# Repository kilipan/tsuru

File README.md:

# 鶴の恩返し (Tsuru No Ongaeshi)
A cute lil 3-row, katana-staggered keyboard with ISO-Enter compat :)

## Versions
As of now there exist two confirmed versions in this repo:
- SAMD21 version (wired, ZMK only, you will have to flash a bootloader!)
- CH552T version (wired, FAK only)

An untested wireless version can be found in the ble branch.

An STM32F072 mod of the original SAMD21 version is available [here](https://github.com/calvin-mcd/tsuru-STM).

## Layout Options
Note: The CH552T version does not support the encoder!

## Firmware
Firmware can be found in my respective repos:
- [FAK config](https://github.com/kilipan/fak-config/tree/main/keyboards/tsuru)
- [ZMK config](https://github.com/kilipan/zmk-config-tsuru)

## Cases
A beatiful wedge case (**NOT** pictured above) was made by DizzySkizzo (`dizzyskizzo1337` on Discord), who graciously allowed me to make it available under the same license. See the `case` directory.

A super fun case with a key strap and transport shell made by krisenplan is available [on printables](https://www.printables.com/de/model/946165-tsuru-travel-keyboard-case)!

Two great cases made by [Seirin-Blu](https://github.com/seirin-blu) are available here:
- [Tsuru MFR2](https://github.com/seirin-blu/Tsuru-MFR2)
- [SK-Tsuru](https://github.com/seirin-blu/SK-Tsuru)

## Availability
All files are provided under CERN-OHL-S license. Feel free to build your own!

## Thanks
Thank you Pete Johanson for letting me use the SAMD21 schematic and zmk config from the [samd21pad](https://github.com/petejohanson/samd21pad/) and for all the help getting the bootloader onto the chip!
This would've never gotten anywhere without your help <3

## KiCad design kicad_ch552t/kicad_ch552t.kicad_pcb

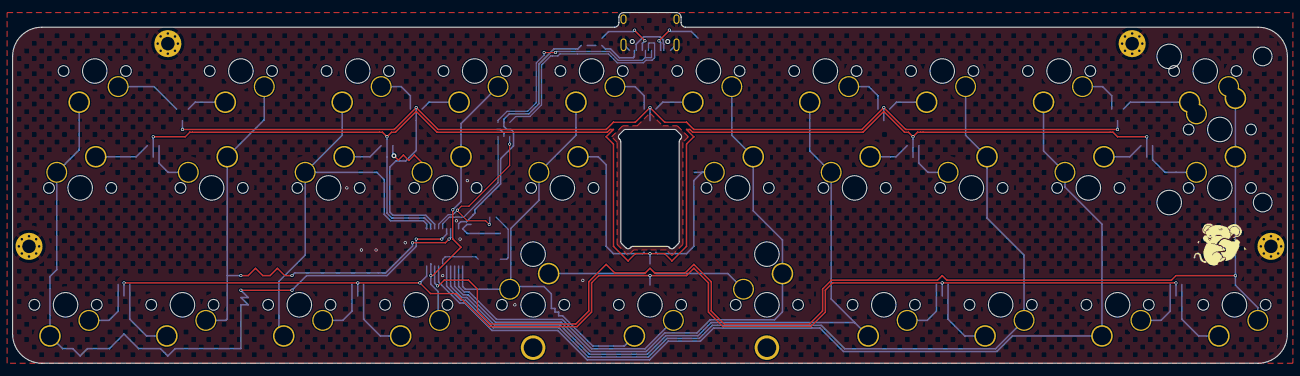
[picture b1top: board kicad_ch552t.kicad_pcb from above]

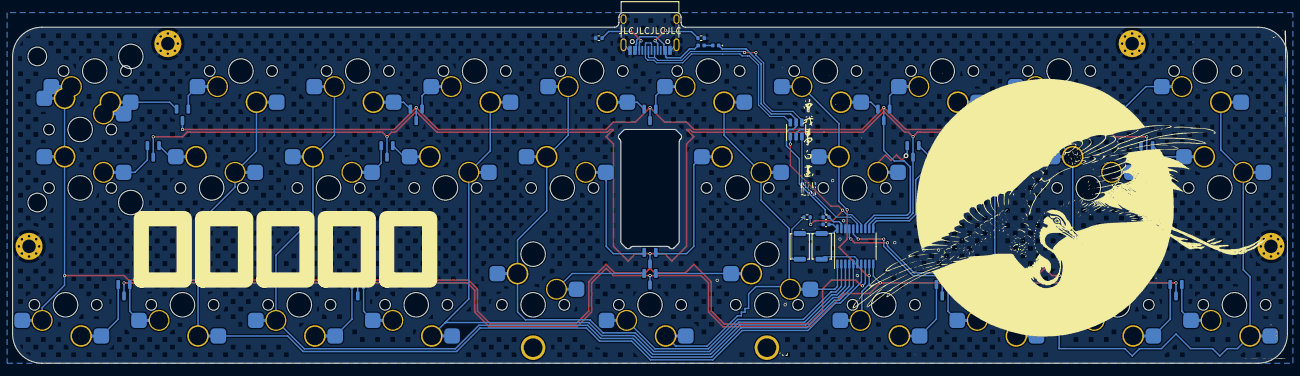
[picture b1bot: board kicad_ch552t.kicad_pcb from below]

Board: 2 copper layers, 207.8 x 57.2 mm, 66 parts (28 on the bottom side), 57 nets.

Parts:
C1, C2: 100nF; C_0402_1005Metric
D1, D2, D3, D4, D5, D6, D7, D8, D9, D10, D11, D12, D13, D14, D15: BAV70_Small; apfel_SOT-23_silkless
D16: PMEG2010EA; D_0402_1005Metric
F1: 500mA; Fuse_0402_1005Metric
H1, H2, H3, H4: MountingHole_Pad; MountingHole_2.2mm_M2_Pad_Via_nosilk
J1: USB_C_Receptacle_USB2.0; USB_C_Receptacle_HRO_TYPE-C-31-M-12
MX1, MX2, MX3, MX4, MX5, MX6, MX7, MX8, MX9, MX10, MX11, MX12, MX13, MX14, MX15, MX16, MX17, MX18, MX19, MX20, MX21, MX22, MX23, MX24, MX25, MX26, MX27, MX28, MX29, MX30, MX31, MX32: MX_SW_HS; MX-HotswapSAFE_no_silk
R1, R2: 5.1k; R_0402_1005Metric
R3: 10k; R_0402_1005Metric
S1: MX_stab; STAB_MX_P_3u
S2: MX_stab; STAB_MX_ISO-ROT
SW1: BOOT; SW_Push_SPST_NO_Alps_SKRK
SW2: RESET; SW_Push_SPST_NO_Alps_SKRK
U1: TSSOP-20_4.4x6.5mm_P0.65mm
U2: USBLC6-2SC6; SOT-23-6
tsuru: LOGO

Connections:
+3.3V: C2.1, SW1.2, SW2.2, U1.20 (V33)
BOOT: R3.2, SW1.1
CC1: J1.A5 (CC1), R1.1
CC2: J1.B5 (CC2), R2.1
GND: C1.2, C2.2, H1.1, H2.1, H3.1, H4.1, J1.A1 (GND), J1.A12 (GND), J1.B1 (GND), J1.B12 (GND), J1.S1 (SHIELD), R1.2, R2.2, U1.18 (GND), U2.2 (GND)
unnamed: D1.1 (A1), MX1.1
unnamed: D1.2 (A2), MX2.2
unnamed: D2.1 (A1), MX3.1
unnamed: D2.2 (A2), MX4.2
unnamed: D3.1 (A1), MX5.1
unnamed: D3.2 (A2), MX6.2
unnamed: D4.1 (A1), MX7.1
unnamed: D4.2 (A2), MX8.2
unnamed: D5.1 (A1), MX9.1
unnamed: D5.2 (A2), MX10.2, MX32.1
unnamed: D6.1 (A1), MX11.2
unnamed: D6.2 (A2), MX12.1
unnamed: D7.1 (A1), MX13.2
unnamed: D7.2 (A2), MX14.1
unnamed: D8.1 (A1), MX15.2
unnamed: D8.2 (A2), MX16.1
unnamed: D9.1 (A1), MX17.2
unnamed: D9.2 (A2), MX18.1
unnamed: D10.1 (A1), MX19.2
unnamed: D10.2 (A2), MX20.1
unnamed: D11.1 (A1), MX21.1
unnamed: D11.2 (A2), MX22.2
unnamed: D12.1 (A1), MX23.1
unnamed: D12.2 (A2), MX24.2
unnamed: D13.1 (A1), MX25.2
unnamed: D13.2 (A2), MX26.1
unnamed: D14.1 (A1), MX27.1
unnamed: D14.2 (A2), MX28.2
unnamed: D15.1 (A1), MX29.1
unnamed: D15.2 (A2), MX30.2
unnamed: D16.2 (A), F1.1
PORT+: J1.A6 (D+), J1.B6 (D+), U2.6 (I/O1)
PORT-: J1.A7 (D-), J1.B7 (D-), U2.4 (I/O2)
RST: SW2.1, U1.6 (RST)
UDM: U1.15 (P3.7), U2.3 (I/O2)
UDP: R3.1, U1.14 (P3.6), U2.1 (I/O1)
VBUS: F1.2, J1.A4 (VBUS), J1.A9 (VBUS), J1.B4 (VBUS), J1.B9 (VBUS)
VCC: C1.1, D16.1 (K), U1.19 (VCC), U2.5 (VBUS)
c0: MX1.2, MX11.1, MX21.2, U1.16 (P1.3)
c1: MX2.1, MX12.2, MX22.1, U1.17 (P1.2)
c2: MX3.2, MX13.1, MX23.2, U1.11 (P3.3)
c3: MX4.1, MX14.2, MX24.1, U1.9 (P3.1)
c4: MX5.2, MX15.1, MX25.1, MX31.2, U1.1 (P3.2)
c5: MX6.1, MX16.2, MX26.2, U1.3 (P1.5)
c6: MX7.2, MX17.1, MX27.2, U1.4 (P1.6)
c7: MX8.1, MX18.2, MX28.1, U1.5 (P1.7)
c8: MX9.2, MX19.1, MX29.2, U1.7 (P1.0)
c9: MX10.1, MX20.2, MX30.1, MX32.2, U1.8 (P1.1)
r0: D1.3 (K), D2.3 (K), D3.3 (K), D4.3 (K), D5.3 (K), U1.13 (P3.5)
r1: D6.3 (K), D7.3 (K), D8.3 (K), D9.3 (K), D10.3 (K), U1.12 (P3.4)
r2: D11.3 (K), D12.3 (K), D13.3 (K), D14.3 (K), D15.3 (K), U1.10 (P3.0)
r3: MX31.1, U1.2 (P1.4)

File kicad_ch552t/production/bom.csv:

Designator,Footprint,Quantity,Value,LCSC Part #
"C1, C2",0402,2,100nF,C1525
"D1, D10, D11, D12, D13, D14, D15, D2, D3, D4, D5, D6, D7, D8, D9",apfel_SOT-23_silkless,15,BAV70_Small,
D16,0402,1,PMEG2010EA,C2837790
F1,0402,1,500mA,C210357
"H1, H2, H3, H4",MountingHole_2.2mm_M2_Pad_Via_nosilk,4,MountingHole_Pad,
J1,USB_C_Receptacle_HRO_TYPE-C-31-M-12,1,USB_C_Receptacle_USB2.0,C2765186
"MX1, MX10, MX11, MX12, MX13, MX14, MX15, MX16, MX17, MX18, MX19, MX2, MX20, MX21, MX22, MX23, MX24, MX25, MX26, MX27, MX28, MX29, MX3, MX30, MX31, MX32, MX4, MX5, MX6, MX7, MX8, MX9",MX-HotswapSAFE_no_silk,32,MX_SW_HS,
"R1, R2",0402,2,5.1k,C25905
R3,0402,1,10k,C25744
S1,STAB_MX_P_3u,1,MX_stab,
S2,STAB_MX_ISO-ROT,1,MX_stab,
SW1,SW_Push_SPST_NO_Alps_SKRK,1,BOOT,C115357
SW2,SW_Push_SPST_NO_Alps_SKRK,1,RESET,C115357
U1,TSSOP-20_4.4x6.5mm_P0.65mm,1,~,C111367
U2,SOT-23-6,1,USBLC6-2SC6,C2687116

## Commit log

2024-02-28 add photo
2024-02-28 fix license file
2024-02-28 add KLE
2024-02-28 fix KLE
2024-03-10 wip ble version
2024-03-10 first 'finished' version
2024-03-11 next iteration
2024-03-15 add production files
2024-03-15 add budget version
2024-04-11 fix hs socket assembly side
2024-04-28 add case; housekeeping
2024-06-01 add holes for reaching pcb screws
2024-06-01 mention krisenplan case
2024-06-18 fix plate file
2024-06-22 Add links to firmware repos to README.md
2024-06-22 add bootloader warning to samd21 in README.md
2024-07-17 Add link to krisenplan case to README.md
